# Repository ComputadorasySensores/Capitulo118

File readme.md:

# Pico Carrier

Un placa de desarrollo simple para Raspberry Pi Pico/W que incorpora la posibilidad de conectar una pantalla OLED SSD1306 (con jumpers para diferentes variantes de alimentación) y un sensor ambiental BMP/BME280.
También expone todos los GPIO de la placa para una fácil conexión de dispositivos adicionales y un pulsador de reset.

Todos los archivos de diseño en Kicad se encuentran publicados junto a un código de ejemplo en MicroPython

# Fabricación

Dentro de la carpeta `fab` encontrarás los archivos individuales Gerber y de perforación, también el archivo `Pico-Carrier-Fab.zip` que incluye todo listo para ordenar a tu fabricante de PCB favorito.

# Paso a paso

La explicación completa la podrás ver en el siguiente video de Youtube:
https://youtu.be/Y6Xd9Z1UVGs

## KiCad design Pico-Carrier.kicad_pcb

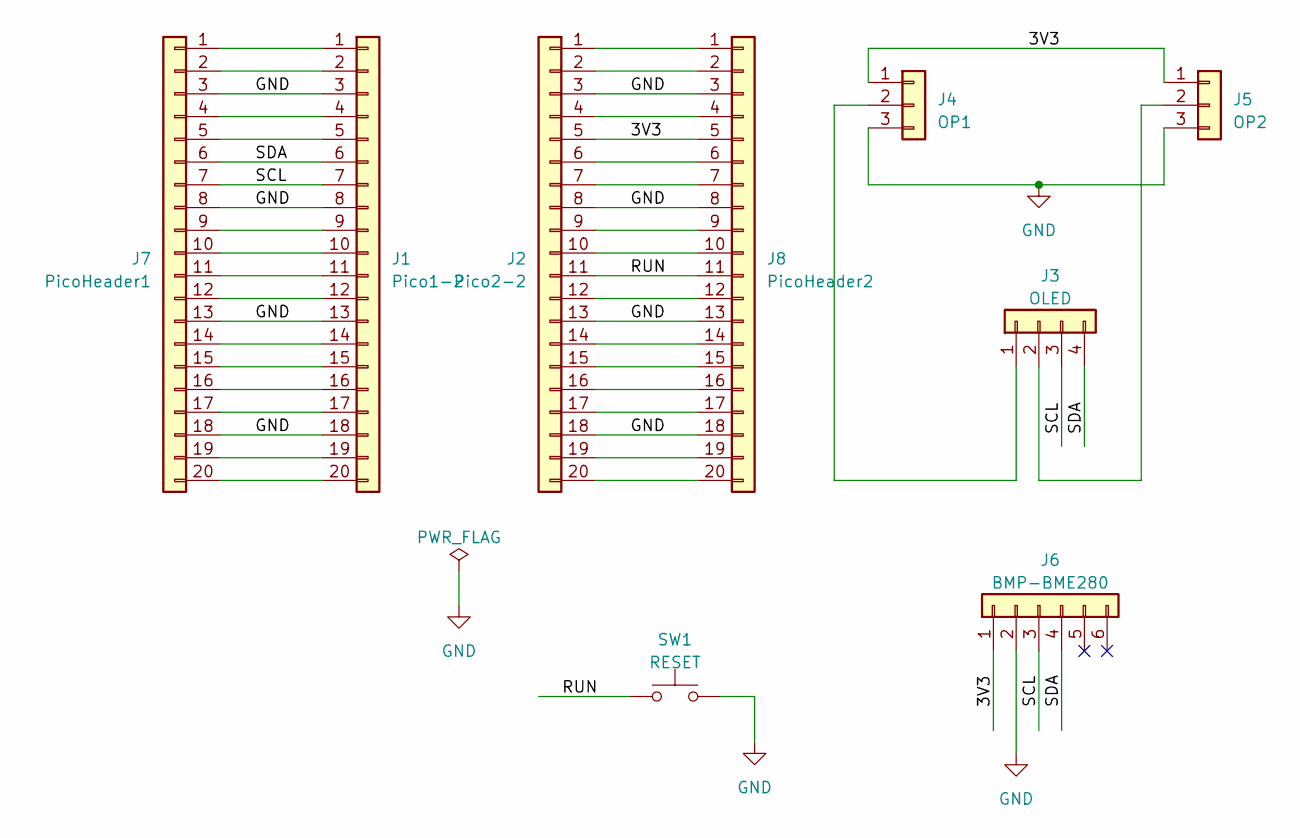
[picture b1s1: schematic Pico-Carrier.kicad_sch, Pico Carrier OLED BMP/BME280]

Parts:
J1: Pico1-2; PinSocket_1x20_P2.54mm_Vertical
J2: Pico2-2; PinSocket_1x20_P2.54mm_Vertical
J3: OLED; PinSocket_1x04_P2.54mm_Vertical
J4: OP1; PinHeader_1x03_P2.54mm_Vertical
J5: OP2; PinHeader_1x03_P2.54mm_Vertical
J6: BMP-BME280; PinSocket_1x06_P2.54mm_Vertical
J7: PicoHeader1; PinHeader_1x20_P2.54mm_Vertical
J8: PicoHeader2; PinHeader_1x20_P2.54mm_Vertical
SW1: RESET; SW_PUSH_6mm

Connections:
/3V3: J2.5, J4.1, J5.1, J6.1, J8.5
/RUN: J2.11, J8.11, SW1.1
/SCL: J1.7, J3.3, J6.3, J7.7
/SDA: J1.6, J3.4, J6.4, J7.6
GND: J1.3, J1.8, J1.13, J1.18, J2.3, J2.8, J2.13, J2.18, J4.3, J5.3, J6.2, J7.3, J7.8, J7.13, J7.18, J8.3, J8.8, J8.13, J8.18, SW1.2
unnamed: J1.1, J7.1
unnamed: J1.2, J7.2
unnamed: J1.4, J7.4
unnamed: J1.5, J7.5
unnamed: J1.9, J7.9
unnamed: J1.10, J7.10
unnamed: J1.11, J7.11
unnamed: J1.12, J7.12
unnamed: J1.14, J7.14
unnamed: J1.15, J7.15
unnamed: J1.16, J7.16
unnamed: J1.17, J7.17
unnamed: J1.19, J7.19
unnamed: J1.20, J7.20
unnamed: J2.1, J8.1
unnamed: J2.2, J8.2
unnamed: J2.4, J8.4
unnamed: J2.6, J8.6
unnamed: J2.7, J8.7
unnamed: J2.9, J8.9
unnamed: J2.10, J8.10
unnamed: J2.12, J8.12
unnamed: J2.14, J8.14
unnamed: J2.15, J8.15
unnamed: J2.16, J8.16
unnamed: J2.17, J8.17
unnamed: J2.19, J8.19
unnamed: J2.20, J8.20
unnamed: J3.1, J4.2
unnamed: J3.2, J5.2

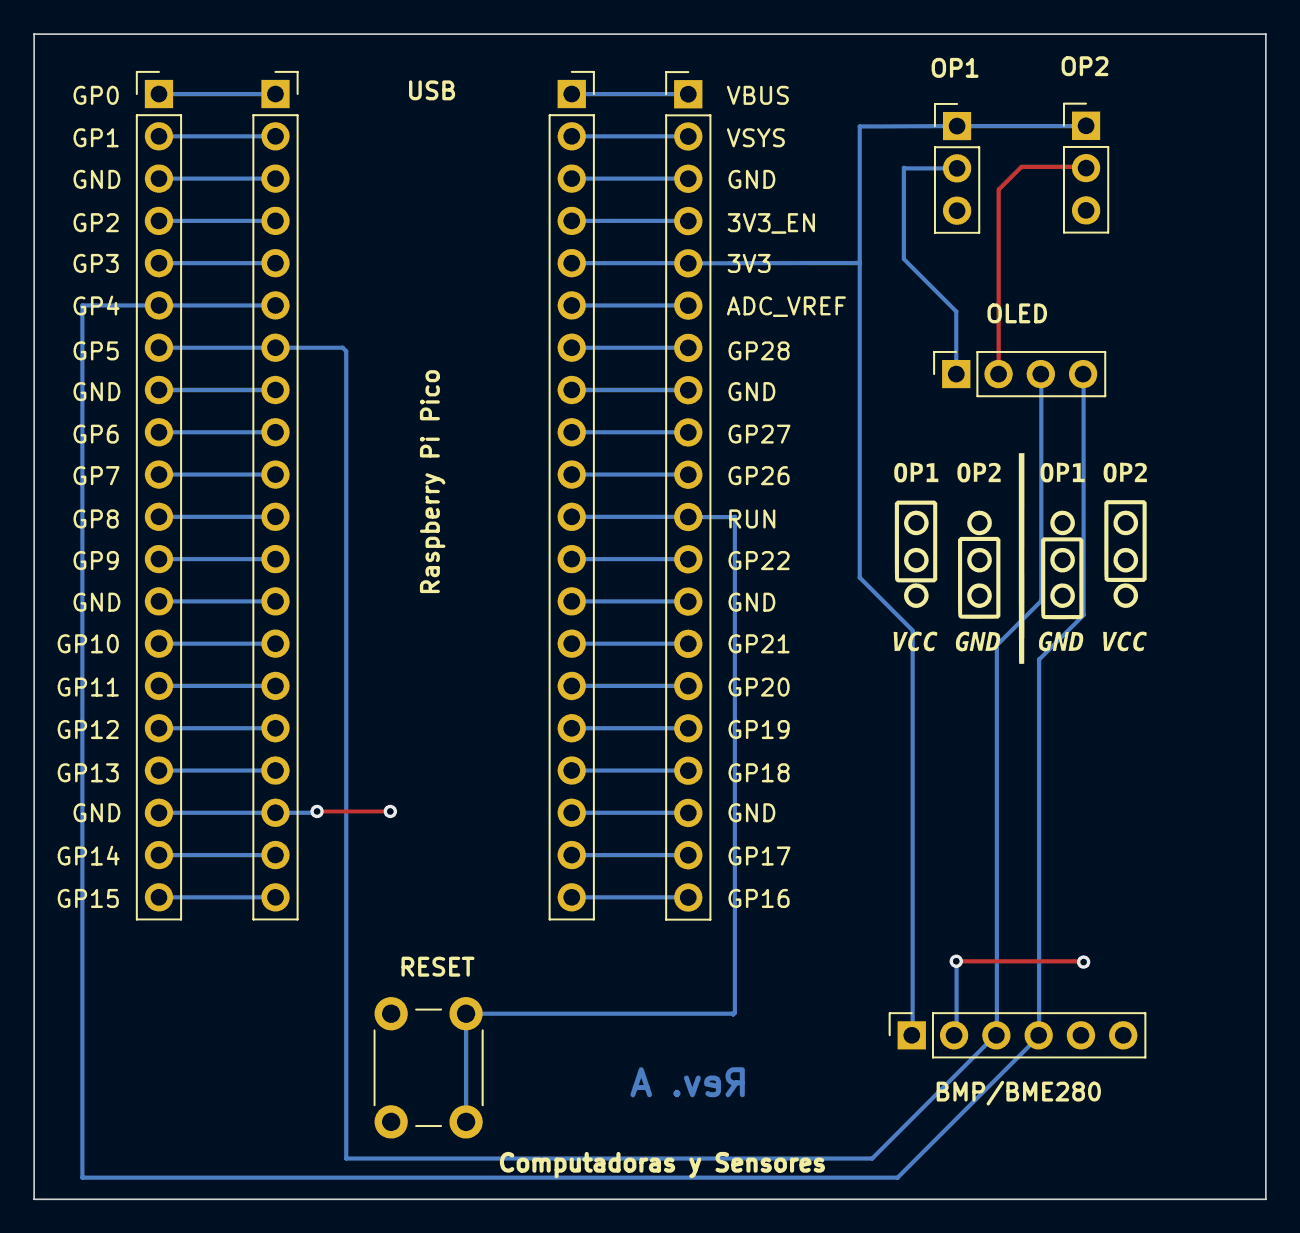
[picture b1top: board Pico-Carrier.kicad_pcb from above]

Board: 2 copper layers, 74.0 x 70.0 mm, 9 parts (0 on the bottom side), 35 nets.
